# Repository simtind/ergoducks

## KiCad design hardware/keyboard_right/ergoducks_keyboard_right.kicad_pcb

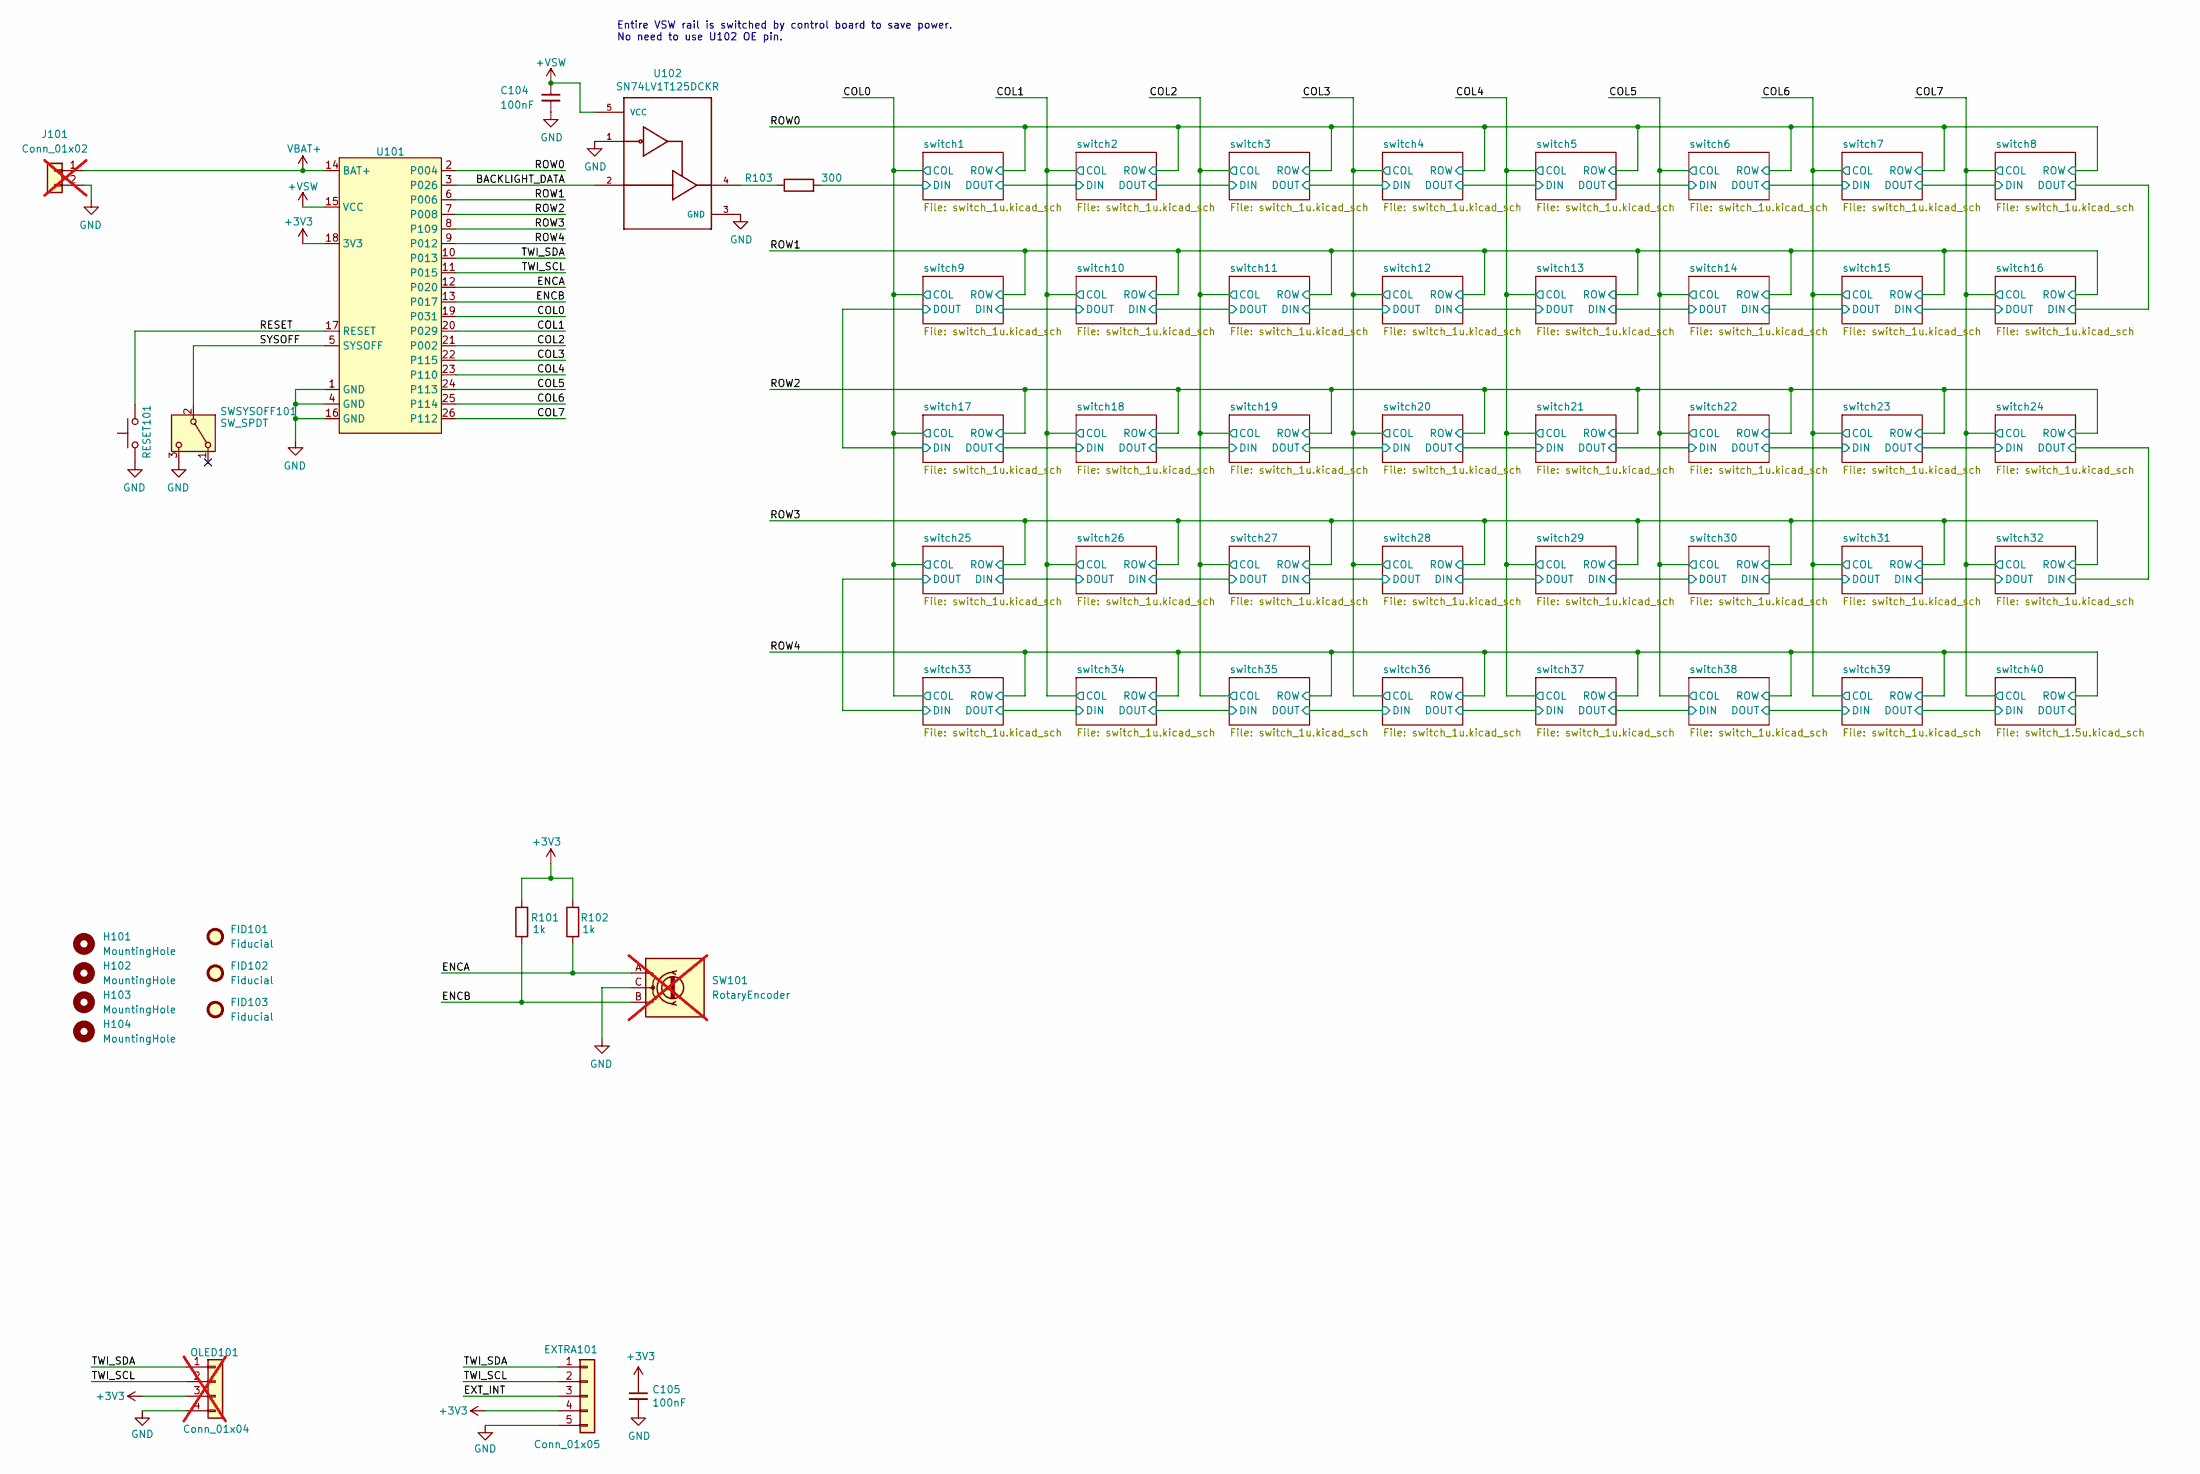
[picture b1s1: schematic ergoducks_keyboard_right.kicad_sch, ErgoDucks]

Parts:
C104, C105: 100nF; C_0402_1005Metric; Mouser partno 187-CL10B104JB8NNNC
EXTRA101: Conn_01x05; PinHeader_1x05_P2.54mm_Vertical
FID101, FID102, FID103: Fiducial; Fiducial_0.5mm_Mask1mm
H101, H102, H103, H104: MountingHole; MountingHole_2.2mm_M2
J101: Conn_01x02; JST_PH_S2B-PH-K_1x02_P2.00mm_Horizontal; not fitted
OLED101: Conn_01x04; PinHeader_1x04_P2.54mm_Vertical; not fitted
R101, R102: 1k; R_0603_1608Metric_Pad0.98x0.95mm_HandSolder; Mouser partno 667-ERJ-H3ED3000V
R103: 300; R_0603_1608Metric_Pad0.98x0.95mm_HandSolder; Mouser partno 667-ERJ-H3ED3000V
RESET101: SW_Push; SW_SPST_B3U-1000P-B; LCSC C561515
SW101: RotaryEncoder; RotaryEncoder_Alps_EC11E-Switch_Vertical_H20mm_MountingHoles; not fitted
SWSYSOFF101: SW_SPDT; SW_SPDT_CK_JS102011SAQN; LCSC C221660
U101: graviton-keycon
U102: SN74LV1T125DCKR; SOT-23-5; Mouser partno 595-SN74LV1T125DCKR

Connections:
+3V3: C105.1, EXTRA101.4, OLED101.3, R101.2, R102.2, U101.18 (3V3)
+VSW: C104.1, U101.15 (VCC), U102.5 (VCC); also elsewhere on the board
/BACKLIGHT_DATA: U101.3 (P026), U102.2
/COL0: U101.19 (P031); also elsewhere on the board
/COL1: U101.20 (P029); also elsewhere on the board
/COL2: U101.21 (P002); also elsewhere on the board
/COL3: U101.22 (P115); also elsewhere on the board
/COL4: U101.23 (P110); also elsewhere on the board
/COL5: U101.24 (P113); also elsewhere on the board
/COL6: U101.25 (P114); also elsewhere on the board
/COL7: U101.26 (P112); also elsewhere on the board
/ENCA: R102.1, SW101.A, U101.12 (P020)
/ENCB: R101.1, SW101.B, U101.13 (P017)
/EXT_INT: EXTRA101.3
/RESET: RESET101.1, U101.17 (RESET)
/ROW0: U101.2 (P004); also elsewhere on the board
/ROW1: U101.6; also elsewhere on the board
/ROW2: U101.7 (P008); also elsewhere on the board
/ROW3: U101.8 (P109); also elsewhere on the board
/ROW4: U101.9 (P012); also elsewhere on the board
/SYSOFF: SWSYSOFF101.2 (B), U101.5 (SYSOFF)
/TWI_SCL: EXTRA101.2, OLED101.2, U101.11 (P015)
/TWI_SDA: EXTRA101.1, OLED101.1, U101.10 (P013)
/switch1/DIN: R103.2; also elsewhere on the board
GND: C104.2, C105.2, EXTRA101.5, J101.2, OLED101.4, RESET101.2, SW101.C, SWSYSOFF101.3 (C), U101.1 (GND), U101.4 (GND), U101.16 (GND), U102.1, U102.3 (GND); also elsewhere on the board
unnamed: R103.1, U102.4
VBAT+: J101.1, U101.14 (BAT+)

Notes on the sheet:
Entire VSW rail is switched by control board to save power. No need to use U102 OE pin.

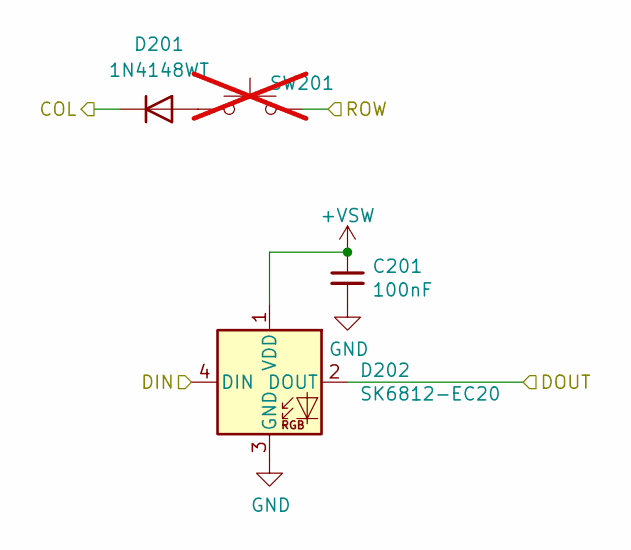
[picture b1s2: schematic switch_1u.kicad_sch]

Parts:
C201: 100nF; C_0402_1005Metric; Mouser partno 187-CL10B104JB8NNNC
D201: 1N4148WT; D_SOD-523; LCSC C27748
D202: SK6812-EC20; sk6812-ec20; Digikey partno 1528-4960-ND
SW201: SW_Hotswap_Kailh_Choc_V1V2_1.00u; Mouser partno 540-MX1A-G1NA; not fitted

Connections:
+VSW: C201.1, D202.1 (VDD); also elsewhere on the board
/COL0: D201.1 (K); also elsewhere on the board
/ROW0: SW201.2; also elsewhere on the board
/switch1/DIN: D202.4 (DIN); also elsewhere on the board
/switch1/DOUT: D202.2 (DOUT); also elsewhere on the board
GND: C201.2, D202.3 (GND); also elsewhere on the board
unnamed: D201.2 (A), SW201.1

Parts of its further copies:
C301, C401, C501, C601, C701, C801, C901, C1001, C1101, C1201, C1301, C1401, C1501, C1601, C1701, C1801, C1901, C2001, C2101, C2201, C2301, C2401, C2501, C2601, C2701, C2801, C2901, C3001, C3101, C3201, C3301, C3401, C3501, C3601, C3701, C3801, C3901, C4001: 100nF; C_0402_1005Metric; Mouser partno 187-CL10B104JB8NNNC
D301, D401, D501, D601, D701, D801, D901, D1001, D1101, D1201, D1301, D1401, D1501, D1601, D1701, D1801, D1901, D2001, D2101, D2201, D2301, D2401, D2501, D2601, D2701, D2801, D2901, D3001, D3101, D3201, D3301, D3401, D3501, D3601, D3701, D3801, D3901, D4001: 1N4148WT; D_SOD-523; LCSC C27748
D302, D402, D502, D602, D702, D802, D902, D1002, D1102, D1202, D1302, D1402, D1502, D1602, D1702, D1802, D1902, D2002, D2102, D2202, D2302, D2402, D2502, D2602, D2702, D2802, D2902, D3002, D3102, D3202, D3302, D3402, D3502, D3602, D3702, D3802, D3902, D4002: SK6812-EC20; sk6812-ec20; Digikey partno 1528-4960-ND
SW301, SW401, SW501, SW601, SW701, SW801, SW901, SW1001, SW1101, SW1201, SW1301, SW1401, SW1501, SW1601, SW1701, SW1801, SW1901, SW2001, SW2101, SW2201, SW2301, SW2401, SW2501, SW2601, SW2701, SW2801, SW2901, SW3001, SW3101, SW3201, SW3301, SW3401, SW3501, SW3601, SW3701, SW3801, SW3901, SW4001: SW_Hotswap_Kailh_Choc_V1V2_1.00u; Mouser partno 540-MX1A-G1NA; not fitted

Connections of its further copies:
+VSW: C301.1, C401.1, C501.1, C601.1, C701.1, C801.1, C901.1, C1001.1, C1101.1, C1201.1, C1301.1, C1401.1, C1501.1, C1601.1, C1701.1, C1801.1, C1901.1, C2001.1, C2101.1, C2201.1, C2301.1, C2401.1, C2501.1, C2601.1, C2701.1, C2801.1, C2901.1, C3001.1, C3101.1, C3201.1, C3301.1, C3401.1, C3501.1, C3601.1, C3701.1, C3801.1, C3901.1, C4001.1, D302.1 (VDD), D402.1 (VDD), D502.1 (VDD), D602.1 (VDD), D702.1 (VDD), D802.1 (VDD), D902.1 (VDD), D1002.1 (VDD), D1102.1 (VDD), D1202.1 (VDD), D1302.1 (VDD), D1402.1 (VDD), D1502.1 (VDD), D1602.1 (VDD), D1702.1 (VDD), D1802.1 (VDD), D1902.1 (VDD), D2002.1 (VDD), D2102.1 (VDD), D2202.1 (VDD), D2302.1 (VDD), D2402.1 (VDD), D2502.1 (VDD), D2602.1 (VDD), D2702.1 (VDD), D2802.1 (VDD), D2902.1 (VDD), D3002.1 (VDD), D3102.1 (VDD), D3202.1 (VDD), D3302.1 (VDD), D3402.1 (VDD), D3502.1 (VDD), D3602.1 (VDD), D3702.1 (VDD), D3802.1 (VDD), D3902.1 (VDD), D4002.1 (VDD); also elsewhere on the board
/COL0: D1001.1 (K), D1801.1 (K), D2601.1 (K), D3401.1 (K); also elsewhere on the board
/COL1: D301.1 (K), D1101.1 (K), D1901.1 (K), D2701.1 (K), D3501.1 (K); also elsewhere on the board
/COL2: D401.1 (K), D1201.1 (K), D2001.1 (K), D2801.1 (K), D3601.1 (K); also elsewhere on the board
/COL3: D501.1 (K), D1301.1 (K), D2101.1 (K), D2901.1 (K), D3701.1 (K); also elsewhere on the board
/COL4: D601.1 (K), D1401.1 (K), D2201.1 (K), D3001.1 (K), D3801.1 (K); also elsewhere on the board
/COL5: D701.1 (K), D1501.1 (K), D2301.1 (K), D3101.1 (K), D3901.1 (K); also elsewhere on the board
/COL6: D801.1 (K), D1601.1 (K), D2401.1 (K), D3201.1 (K), D4001.1 (K); also elsewhere on the board
/COL7: D901.1 (K), D1701.1 (K), D2501.1 (K), D3301.1 (K); also elsewhere on the board
/ROW0: SW301.2, SW401.2, SW501.2, SW601.2, SW701.2, SW801.2, SW901.2; also elsewhere on the board
/ROW1: SW1001.2, SW1101.2, SW1201.2, SW1301.2, SW1401.2, SW1501.2, SW1601.2, SW1701.2; also elsewhere on the board
/ROW2: SW1801.2, SW1901.2, SW2001.2, SW2101.2, SW2201.2, SW2301.2, SW2401.2, SW2501.2; also elsewhere on the board
/ROW3: SW2601.2, SW2701.2, SW2801.2, SW2901.2, SW3001.2, SW3101.2, SW3201.2, SW3301.2; also elsewhere on the board
/ROW4: SW3401.2, SW3501.2, SW3601.2, SW3701.2, SW3801.2, SW3901.2, SW4001.2; also elsewhere on the board
/switch1/DOUT: D302.4 (DIN); also elsewhere on the board
/switch2/DOUT: D302.2 (DOUT), D402.4 (DIN)
/switch3/DOUT: D402.2 (DOUT), D502.4 (DIN)
/switch4/DOUT: D502.2 (DOUT), D602.4 (DIN)
/switch5/DOUT: D602.2 (DOUT), D702.4 (DIN)
/switch6/DOUT: D702.2 (DOUT), D802.4 (DIN)
/switch7/DOUT: D802.2 (DOUT), D902.4 (DIN)
/switch10/DIN: D1102.4 (DIN), D1202.2 (DOUT)
/switch10/DOUT: D1002.4 (DIN), D1102.2 (DOUT)
/switch11/DIN: D1202.4 (DIN), D1302.2 (DOUT)
/switch12/DIN: D1302.4 (DIN), D1402.2 (DOUT)
/switch13/DIN: D1402.4 (DIN), D1502.2 (DOUT)
/switch14/DIN: D1502.4 (DIN), D1602.2 (DOUT)
/switch15/DIN: D1602.4 (DIN), D1702.2 (DOUT)
/switch16/DIN: D902.2 (DOUT), D1702.4 (DIN)
/switch17/DIN: D1002.2 (DOUT), D1802.4 (DIN)
/switch17/DOUT: D1802.2 (DOUT), D1902.4 (DIN)
/switch18/DOUT: D1902.2 (DOUT), D2002.4 (DIN)
/switch19/DOUT: D2002.2 (DOUT), D2102.4 (DIN)
/switch20/DOUT: D2102.2 (DOUT), D2202.4 (DIN)
/switch21/DOUT: D2202.2 (DOUT), D2302.4 (DIN)
/switch22/DOUT: D2302.2 (DOUT), D2402.4 (DIN)
/switch23/DOUT: D2402.2 (DOUT), D2502.4 (DIN)
/switch24/DOUT: D2502.2 (DOUT), D3302.4 (DIN)
/switch25/DIN: D2602.4 (DIN), D2702.2 (DOUT)
/switch25/DOUT: D2602.2 (DOUT), D3402.4 (DIN)
/switch26/DIN: D2702.4 (DIN), D2802.2 (DOUT)
/switch27/DIN: D2802.4 (DIN), D2902.2 (DOUT)
/switch28/DIN: D2902.4 (DIN), D3002.2 (DOUT)
/switch29/DIN: D3002.4 (DIN), D3102.2 (DOUT)
/switch30/DIN: D3102.4 (DIN), D3202.2 (DOUT)
/switch31/DIN: D3202.4 (DIN), D3302.2 (DOUT)
/switch33/DOUT: D3402.2 (DOUT), D3502.4 (DIN)
/switch34/DOUT: D3502.2 (DOUT), D3602.4 (DIN)
/switch35/DOUT: D3602.2 (DOUT), D3702.4 (DIN)
/switch36/DOUT: D3702.2 (DOUT), D3802.4 (DIN)
/switch37/DOUT: D3802.2 (DOUT), D3902.4 (DIN)
/switch38/DOUT: D3902.2 (DOUT), D4002.4 (DIN)
/switch39/DOUT: D4002.2 (DOUT); also elsewhere on the board
GND: C301.2, C401.2, C501.2, C601.2, C701.2, C801.2, C901.2, C1001.2, C1101.2, C1201.2, C1301.2, C1401.2, C1501.2, C1601.2, C1701.2, C1801.2, C1901.2, C2001.2, C2101.2, C2201.2, C2301.2, C2401.2, C2501.2, C2601.2, C2701.2, C2801.2, C2901.2, C3001.2, C3101.2, C3201.2, C3301.2, C3401.2, C3501.2, C3601.2, C3701.2, C3801.2, C3901.2, C4001.2, D302.3 (GND), D402.3 (GND), D502.3 (GND), D602.3 (GND), D702.3 (GND), D802.3 (GND), D902.3 (GND), D1002.3 (GND), D1102.3 (GND), D1202.3 (GND), D1302.3 (GND), D1402.3 (GND), D1502.3 (GND), D1602.3 (GND), D1702.3 (GND), D1802.3 (GND), D1902.3 (GND), D2002.3 (GND), D2102.3 (GND), D2202.3 (GND), D2302.3 (GND), D2402.3 (GND), D2502.3 (GND), D2602.3 (GND), D2702.3 (GND), D2802.3 (GND), D2902.3 (GND), D3002.3 (GND), D3102.3 (GND), D3202.3 (GND), D3302.3 (GND), D3402.3 (GND), D3502.3 (GND), D3602.3 (GND), D3702.3 (GND), D3802.3 (GND), D3902.3 (GND), D4002.3 (GND); also elsewhere on the board
unnamed: D301.2 (A), SW301.1
unnamed: D401.2 (A), SW401.1
unnamed: D501.2 (A), SW501.1
unnamed: D601.2 (A), SW601.1
unnamed: D701.2 (A), SW701.1
unnamed: D801.2 (A), SW801.1
unnamed: D901.2 (A), SW901.1
unnamed: D1001.2 (A), SW1001.1
unnamed: D1101.2 (A), SW1101.1
unnamed: D1201.2 (A), SW1201.1
unnamed: D1301.2 (A), SW1301.1
unnamed: D1401.2 (A), SW1401.1
unnamed: D1501.2 (A), SW1501.1
unnamed: D1601.2 (A), SW1601.1
unnamed: D1701.2 (A), SW1701.1
unnamed: D1801.2 (A), SW1801.1
unnamed: D1901.2 (A), SW1901.1
unnamed: D2001.2 (A), SW2001.1
unnamed: D2101.2 (A), SW2101.1
unnamed: D2201.2 (A), SW2201.1
unnamed: D2301.2 (A), SW2301.1
unnamed: D2401.2 (A), SW2401.1
unnamed: D2501.2 (A), SW2501.1
unnamed: D2601.2 (A), SW2601.1
unnamed: D2701.2 (A), SW2701.1
unnamed: D2801.2 (A), SW2801.1
unnamed: D2901.2 (A), SW2901.1
unnamed: D3001.2 (A), SW3001.1
unnamed: D3101.2 (A), SW3101.1
unnamed: D3201.2 (A), SW3201.1
unnamed: D3301.2 (A), SW3301.1
unnamed: D3401.2 (A), SW3401.1
unnamed: D3501.2 (A), SW3501.1
unnamed: D3601.2 (A), SW3601.1
unnamed: D3701.2 (A), SW3701.1
unnamed: D3801.2 (A), SW3801.1
unnamed: D3901.2 (A), SW3901.1
unnamed: D4001.2 (A), SW4001.1

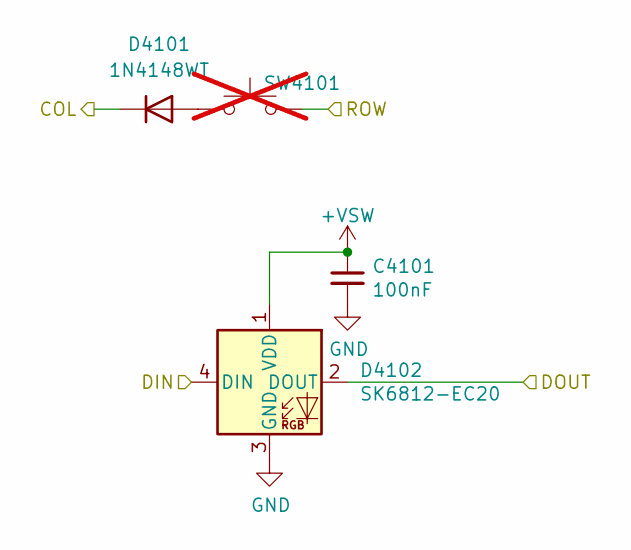
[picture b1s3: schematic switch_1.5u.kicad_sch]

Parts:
C4101: 100nF; C_0402_1005Metric; Mouser partno 187-CL10B104JB8NNNC
D4101: 1N4148WT; D_SOD-523; LCSC C27748
D4102: SK6812-EC20; sk6812-ec20; Digikey partno 1528-4960-ND
SW4101: SW_Hotswap_Kailh_Choc_V1V2_1.50u; Mouser partno 540-MX1A-G1NA; not fitted

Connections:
+VSW: C4101.1, D4102.1 (VDD); also elsewhere on the board
/COL7: D4101.1 (K); also elsewhere on the board
/ROW4: SW4101.2; also elsewhere on the board
/switch39/DOUT: D4102.4 (DIN); also elsewhere on the board
/switch40/DOUT: D4102.2 (DOUT)
GND: C4101.2, D4102.3 (GND); also elsewhere on the board
unnamed: D4101.2 (A), SW4101.1

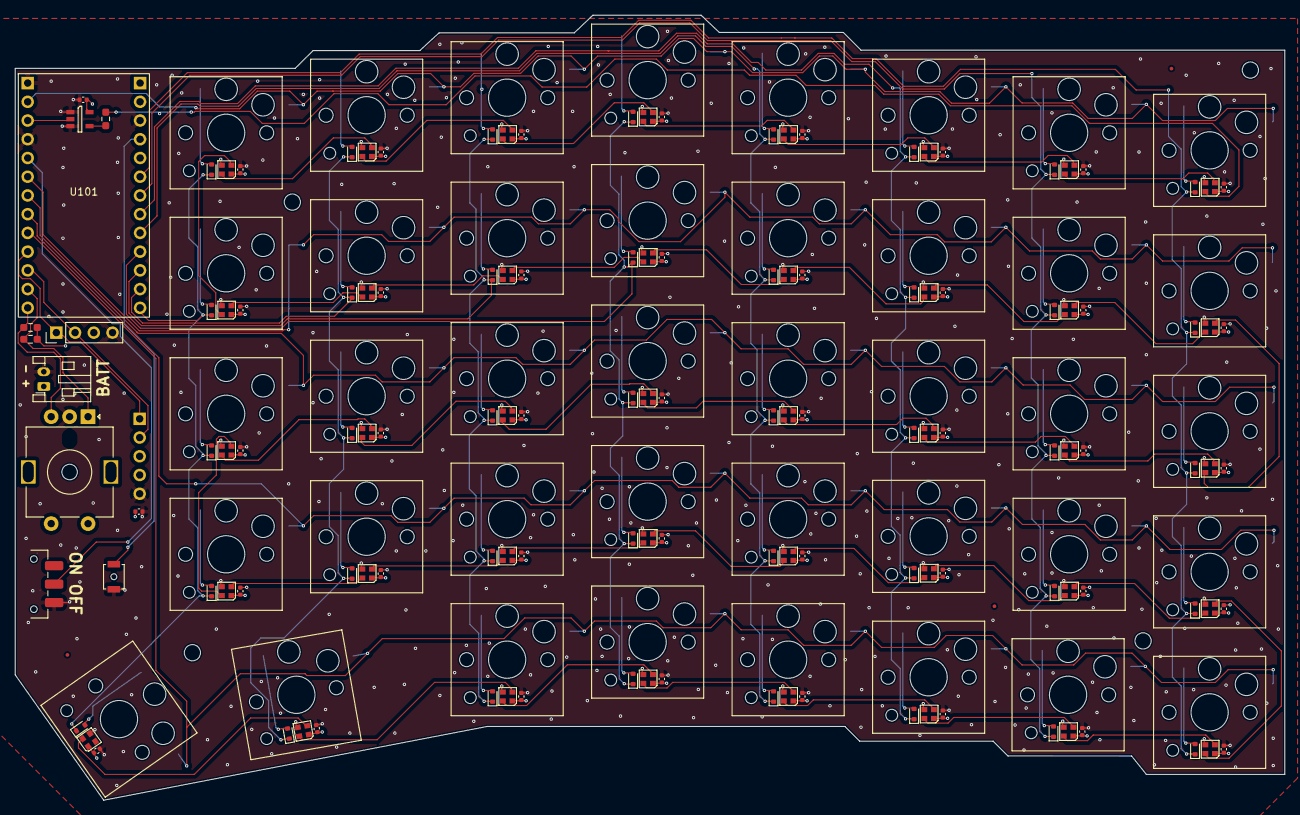
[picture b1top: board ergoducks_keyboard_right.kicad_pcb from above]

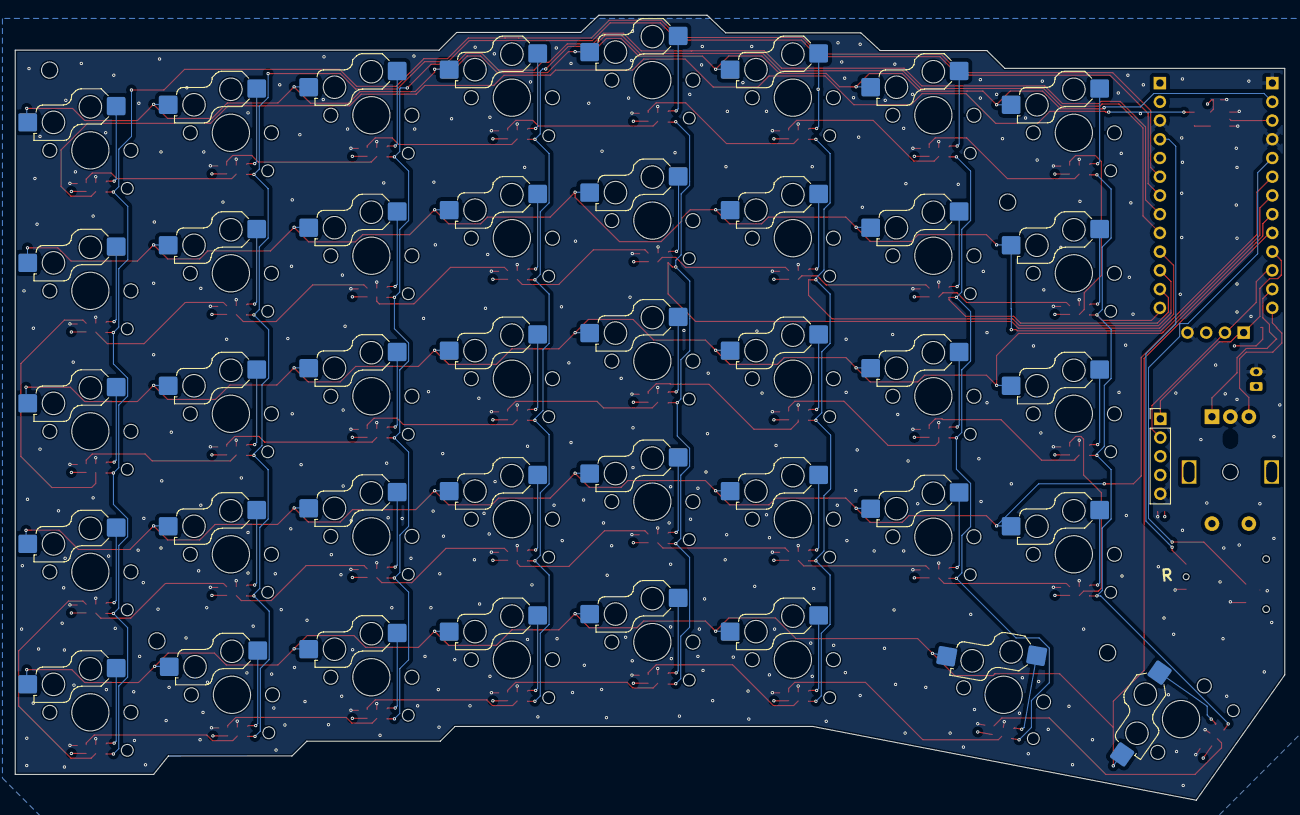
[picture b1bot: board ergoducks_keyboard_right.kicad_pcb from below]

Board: 4 copper layers, 172.1 x 106.4 mm, 180 parts (2 on the bottom side), 105 nets.

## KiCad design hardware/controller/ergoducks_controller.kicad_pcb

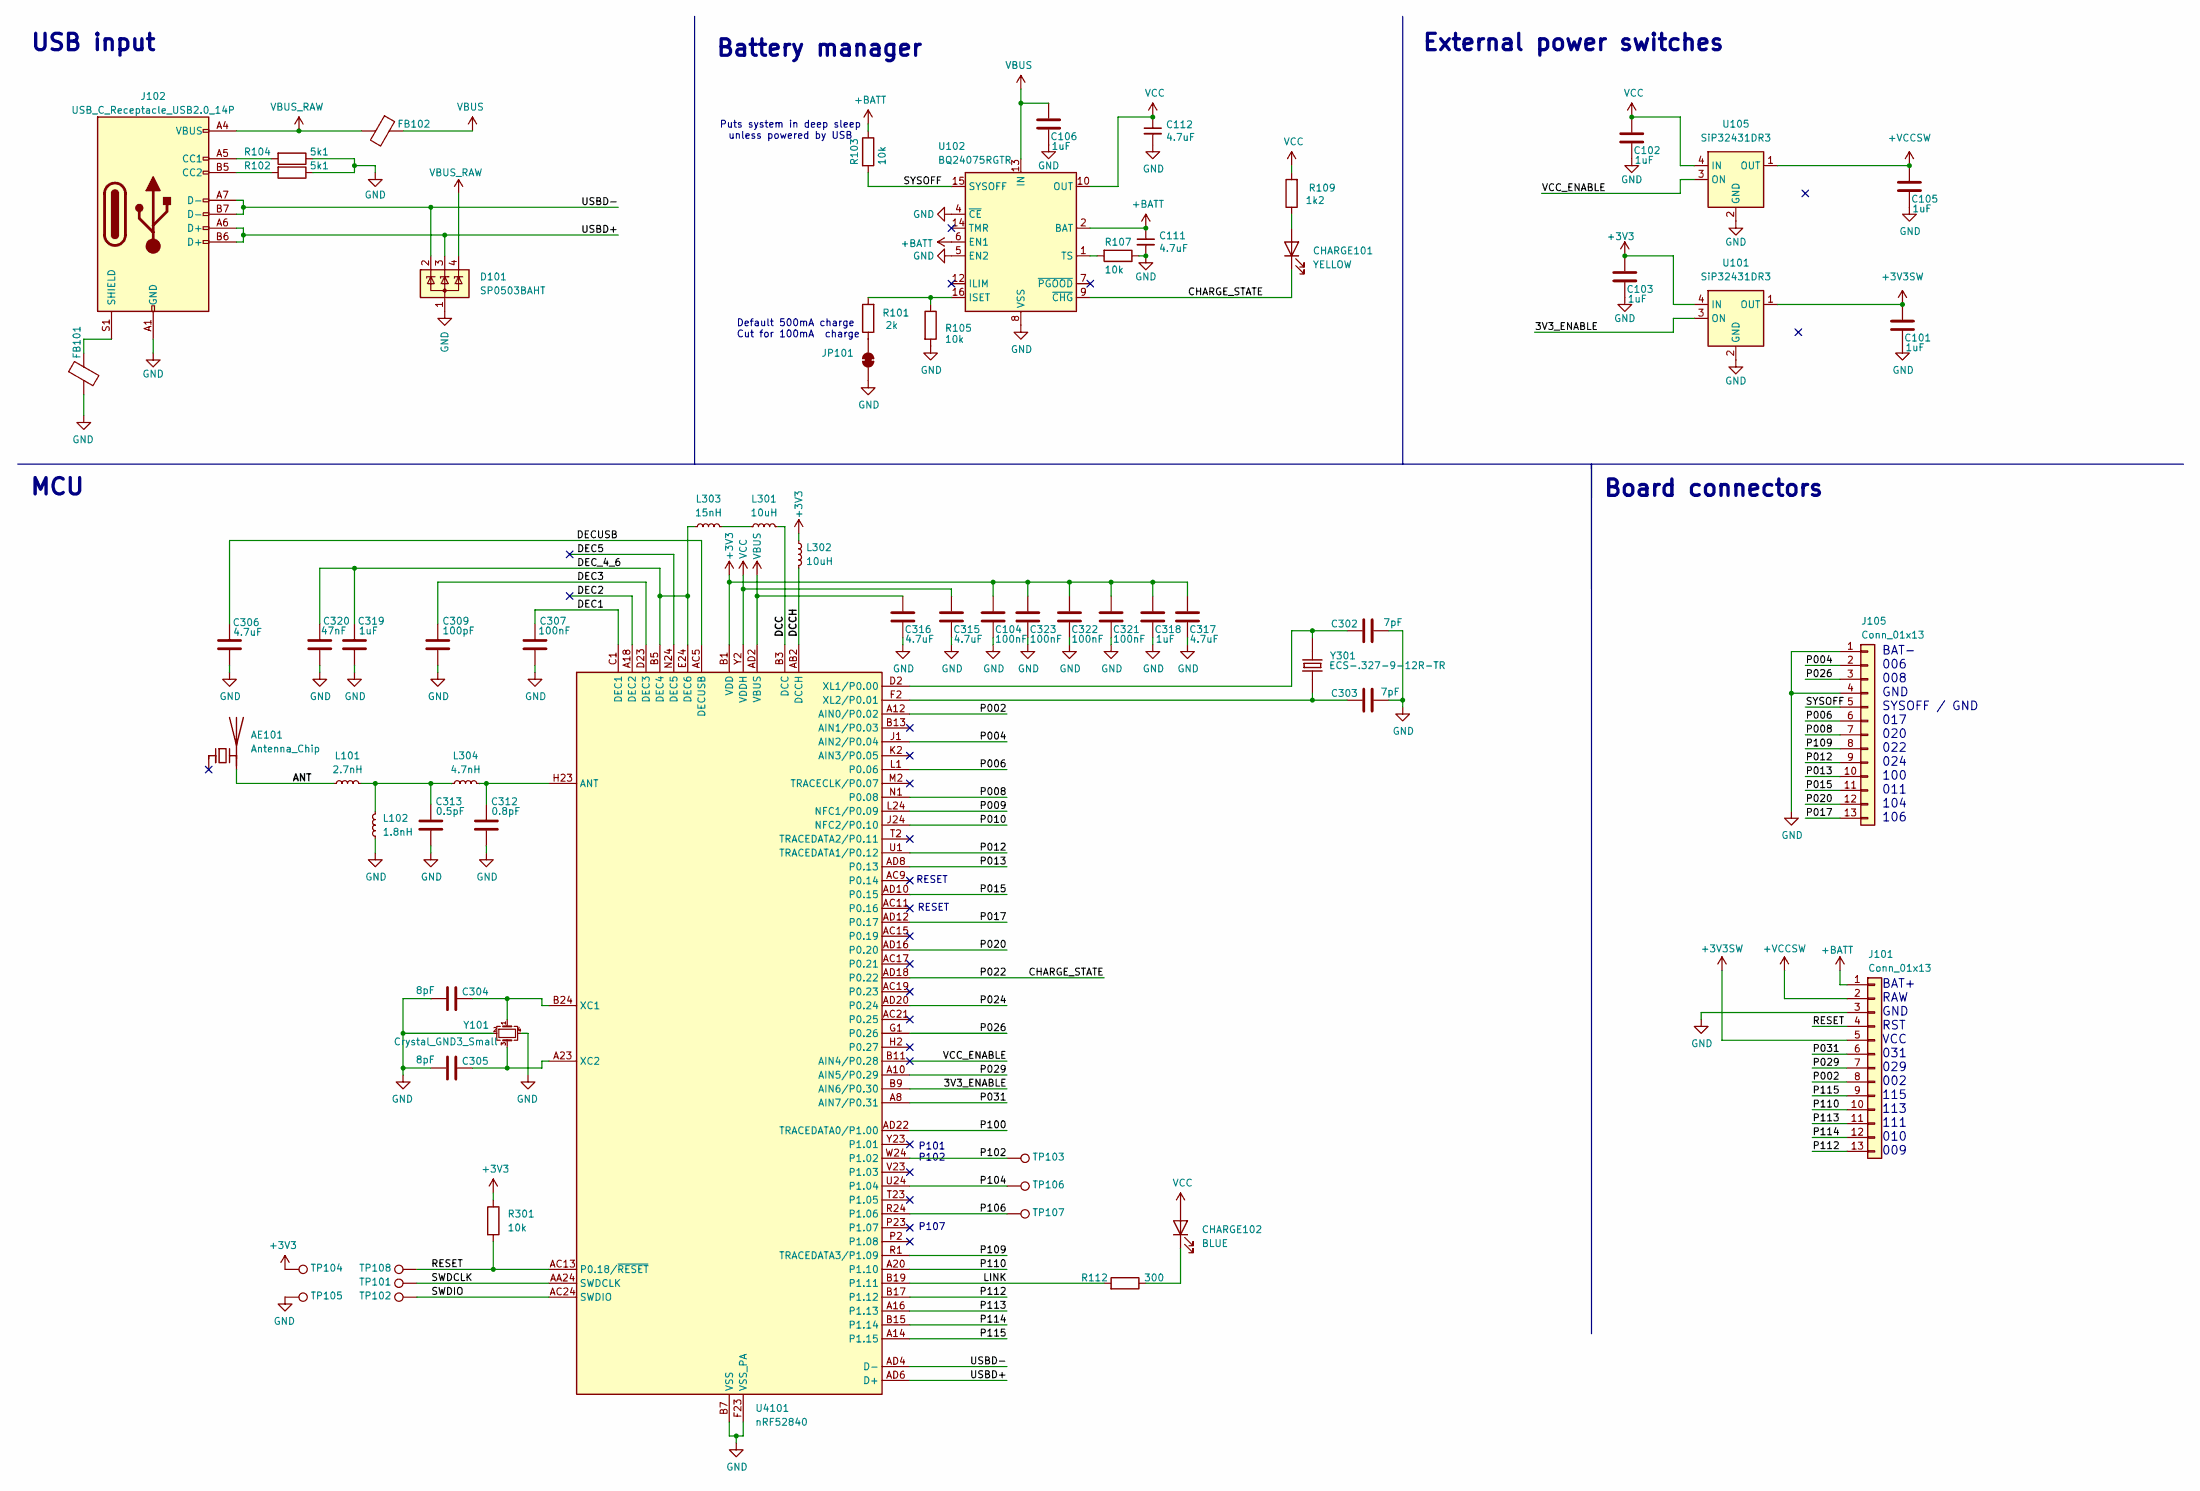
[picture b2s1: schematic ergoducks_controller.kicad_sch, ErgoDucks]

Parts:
AE101: Antenna_Chip; Johanson_2450AT43F0100_wwithpads_cortyard; Part Number 2450AT43B100E; LCSC C2917721
C101, C102, C103, C105, C106, C318, C319: 1uF; C_0201_0603Metric; Part Number GRM033R61A105ME44D; LCSC C76935
C104, C307, C321, C322, C323: 100nF; C_0201_0603Metric; Part Number GRM033Z71C104KE14D; LCSC C668346
C111, C112: 4.7uF; C_0402_1005Metric; Mouser partno 187-CL10A475KQ8NNNC
C302, C303: 7pF; C_0201_0603Metric; Part Number GRM0335C1H7R0BA01D; LCSC C161436
C304, C305: 8pF; C_0201_0603Metric; Part Number GRM0335C1H8R0BA01D; LCSC C237417
C306, C315, C316, C317: 4.7uF; C_0402_1005Metric; Part Number GRM155R61E475ME15DGRM155R61E475ME15D; LCSC C2858031
C309: 100pF; C_0201_0603Metric; Part Number GRM0335C1H101JA01D; LCSC C76922
C312: 0.8pF; C_0201_0603Metric; Part Number GRM0335C1HR80WA01D; LCSC C385012
C313: 0.5pF; C_0201_0603Metric; Part Number GRM0335C1HR50BA01D; LCSC C85920
C320: 47nF; C_0201_0603Metric; Part Number GRM033C80J473KE19D; LCSC C782148
CHARGE101: YELLOW; D_0402_1005Metric; Part Number XL-1005UYC; LCSC C25503856
CHARGE102: BLUE; D_0402_1005Metric; Part Number SZYY0402B; LCSC C434447
D101: SP0503BAHT; SOT-143; Part Number SP0503BAHTG; LCSC C7074
FB101, FB102: 120R/0.55A; R_0201_0603Metric; Mouser partno 673-PE-0603PFB121ST
J101, J105: Conn_01x13; PinHeader_1x13_P2.54mm_Vertical
J102: USB_C_Receptacle_USB2.0_14P; JAE_DX07B024JJ2R1500; Part Number DX07B024JJ1R1500; LCSC C2977280
JP101: Cut for 100mA charge; SolderJumper-2_P1mm_Bridged_RoundedPad0.8x1mm
L101: 2.7nH; L_0201_0603Metric; Part Number LQP03TN2N7B02D; LCSC C98043
L102: 1.8nH; L_0201_0603Metric; Part Number LQP03TN1N8B02D; LCSC C98040
L301, L302: 10uH; L_0603_1608Metric; Part Number LQM18FN100M00D; LCSC C86083
L303: 15nH; L_0402_1005Metric; Part Number LQG15HS15NJ02D; LCSC C86059
L304: 4.7nH; L_0201_0603Metric; Part Number LQP03HQ4N7H02D; LCSC C237443
R101: 2k; R_0201_0603Metric; Mouser partno 667-ERJ-H3ED3000V
R102, R104: 5k1; R_0201_0603Metric; Mouser partno 603-RC0603JR-075K1L
R103, R105, R107: 10k; R_0201_0603Metric; Mouser partno 667-ERJ-H3ED1002V
R109: 1k2; R_0201_0603Metric; Mouser partno 667-ERJ-H3ED3000V
R112: 300; R_0201_0603Metric; Mouser partno 667-ERJ-H3ED3000V
R301: 10k; R_0201_0603Metric; Part Number RC0201FR-0710KL; LCSC C106225
TP101, TP108: SWDCLK; TestPoint_Pad_D1.0mm
TP102: SWDIO; TestPoint_Pad_D1.0mm
TP103, TP104, TP106, TP107: 3V3; TestPoint_Pad_D1.0mm
TP105: GND; TestPoint_Pad_D1.0mm
U101, U105: SiP32431DR3; SOT-363_SC-70-6; Part Number SIP32431DR3-T1GE3; LCSC C141606
U102: BQ24075RGTR; VQFN-16-1EP_3x3mm_P0.5mm_EP1.6x1.6mm; Mouser partno 595-BQ24079TRGTR; Digikey partno 296-BQ24079QWRGTRQ1CT-ND
U4101: nRF52840; Nordic_AQFN-73-1EP_7x7mm_P0.5mm; Part Number NRF52840-QIAA-R; LCSC C190794
Y101: Crystal_GND3_Small; Crystal_SMD_SeikoEpson_FA128-4Pin_2.0x1.6mm; Part Number Q22FA12800025; LCSC C187794
Y301: ECS-.327-9-12R-TR; Crystal_SMD_2012-2Pin_2.0x1.2mm_HandSoldering; Mouser partno 520-.327-9-12R-T

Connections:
+3V3: C103.2, C104.2, C317.2, C318.2, C321.2, C322.2, C323.2, L302.1, R301.1, TP104.1, U101.4 (IN), U4101.A22 (VDD), U4101.AD14 (VDD), U4101.AD23 (VDD), U4101.B1 (VDD), U4101.W1 (VDD)
+3V3SW: C101.2, J101.5, U101.1 (OUT)
+BATT: C111.1, J101.1, R103.1, U102.2 (BAT), U102.3 (BAT), U102.6 (EN1)
+VCCSW: C105.2, J101.2, U105.1 (OUT)
/3V3_ENABLE: U101.3 (ON), U4101.B9 (AIN6/P0.30)
/ANT: AE101.2 (PCB_Trace), L101.1
/CHARGE_STATE: CHARGE101.1 (K), U102.9 (~CHG), U4101.AD18 (P0.22)
/DCC: L301.2, U4101.B3 (DCC)
/DCCH: L302.2, U4101.AB2 (DCCH)
/DEC1: C307.2, U4101.C1 (DEC1)
/DEC2: U4101.A18 (DEC2)
/DEC3: C309.2, U4101.D23 (DEC3)
/DEC5: U4101.N24 (DEC5)
/DECUSB: C306.2, U4101.AC5 (DECUSB)
/DEC_4_6: C319.2, C320.2, L303.1, U4101.B5 (DEC4), U4101.E24 (DEC6)
/LINK: R112.2, U4101.B19 (P1.11)
/P002: J101.8, U4101.A12 (AIN0/P0.02)
/P004: J105.2, U4101.J1 (AIN2/P0.04)
/P006: J105.6, U4101.L1 (P0.06)
/P008: J105.7, U4101.N1 (P0.08)
/P009: U4101.L24 (NFC1/P0.09)
/P010: U4101.J24 (NFC2/P0.10)
/P012: J105.9, U4101.U1 (TRACEDATA1/P0.12)
/P013: J105.10, U4101.AD8 (P0.13)
/P015: J105.11, U4101.AD10 (P0.15)
/P017: J105.13, U4101.AD12 (P0.17)
/P020: J105.12, U4101.AD16 (P0.20)
/P024: U4101.AD20 (P0.24)
/P026: J105.3, U4101.G1 (P0.26)
/P029: J101.7, U4101.A10 (AIN5/P0.29)
/P031: J101.6, U4101.A8 (AIN7/P0.31)
/P100: U4101.AD22 (TRACEDATA0/P1.00)
/P102: TP103.1, U4101.W24 (P1.02)
/P104: TP106.1, U4101.U24 (P1.04)
/P106: TP107.1, U4101.R24 (P1.06)
/P109: J105.8, U4101.R1 (TRACEDATA3/P1.09)
/P110: J101.10, U4101.A20 (P1.10)
/P112: J101.13, U4101.B17 (P1.12)
/P113: J101.11, U4101.A16 (P1.13)
/P114: J101.12, U4101.B15 (P1.14)
/P115: J101.9, U4101.A14 (P1.15)
/RESET: J101.4, R301.2, TP108.1, U4101.AC13 (P0.18/~RESET)
/SWDCLK: TP101.1, U4101.AA24 (SWDCLK)
/SWDIO: TP102.1, U4101.AC24 (SWDIO)
/SYSOFF: J105.5, R103.2, U102.15 (SYSOFF)
/USBD+: D101.3 (K), J102.A6 (D+), J102.B6 (D+), U4101.AD6 (D+)
/USBD-: D101.2 (K), J102.A7 (D-), J102.B7 (D-), U4101.AD4 (D-)
/VCC_ENABLE: U105.3 (ON), U4101.B11 (AIN4/P0.28)
GND: C101.1, C102.1, C103.1, C104.1, C105.1, C106.1, C111.2, C112.2, C302.2, C303.2, C304.2, C305.2, C306.1, C307.1, C309.1, C312.1, C313.1, C315.1, C316.1, C317.1, C318.1, C319.1, C320.1, C321.1, C322.1, C323.1, D101.1 (A), FB101.2, J101.3, J102.A1 (GND), J102.A12 (GND), J102.B1 (GND), J102.B12 (GND), J105.1, J105.4, JP101.1 (A), L102.1, R102.1, R104.1, R105.2, R107.1, TP105.1, U101.2 (GND), U101.5 (GND), U102.4 (~CE), U102.5 (EN2), U102.8 (VSS), U102.17 (VSS), U105.2 (GND), U105.5 (GND), U4101.B7 (VSS), U4101.EP (VSS), U4101.F23 (VSS_PA), Y101.2, Y101.4
unnamed: C313.2, L101.2, L102.2, L304.1
unnamed: CHARGE101.2 (A), R109.1
unnamed: CHARGE102.1 (K), R112.1
unnamed: J102.A5 (CC1), R104.2
unnamed: J102.B5 (CC2), R102.2
unnamed: FB101.1, J102.S1 (SHIELD)
unnamed: JP101.2 (B), R101.1
unnamed: L301.1, L303.2
unnamed: R101.2, R105.1, U102.16 (ISET)
unnamed: R107.2, U102.1 (TS)
unnamed: C312.2, L304.2, U4101.H23 (ANT)
unnamed: C304.1, U4101.B24 (XC1), Y101.1
unnamed: C305.1, U4101.A23 (XC2), Y101.3
unnamed: C302.1, U4101.D2 (XL1/P0.00), Y301.1
unnamed: C303.1, U4101.F2 (XL2/P0.01), Y301.2
VBUS: C106.2, C316.2, FB102.1, U102.13 (IN), U4101.AD2 (VBUS)
VBUS_RAW: D101.4 (K), FB102.2, J102.A4 (VBUS), J102.A9 (VBUS), J102.B4 (VBUS), J102.B9 (VBUS)
VCC: C102.2, C112.1, C315.2, CHARGE102.2 (A), R109.2, U102.10 (OUT), U102.11 (OUT), U105.4 (IN), U4101.Y2 (VDDH)

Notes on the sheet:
USB input
BAT+ RAW GND RST VCC 031 029 002 115 113 111 010 009
Default 500mA charge Cut for 100mA charge
External power switches
P101 P102
MCU
P107
RESET
Battery manager
BAT- 006 008 GND SYSOFF / GND 017 020 022 024 100 011 104 106
Puts system in deep sleep unless powered by USB
Board connectors

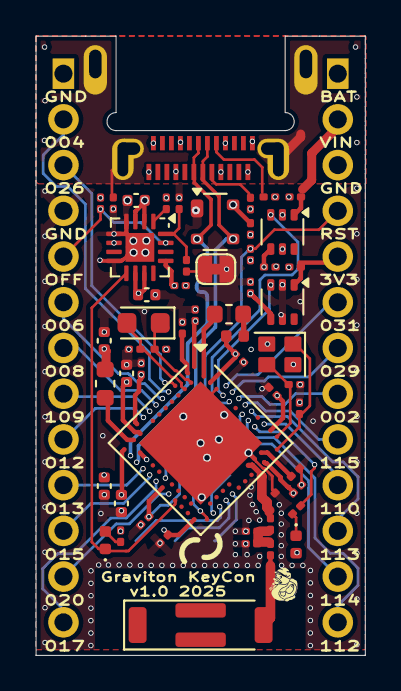
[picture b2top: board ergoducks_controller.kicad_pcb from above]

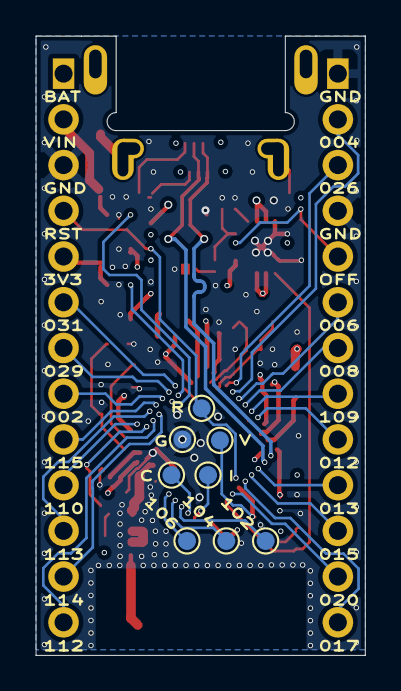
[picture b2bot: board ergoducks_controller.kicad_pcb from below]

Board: 6 copper layers, 18.3 x 34.4 mm, 65 parts (10 on the bottom side), 61 nets.

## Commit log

2025-08-08 Check in project
2025-08-08 Add auto-saved version of pcb.
2025-09-15 Start rev 2
2025-09-15 Add keyboard layout
2025-09-15 Update keyboard layout
2025-12-31 Update after producion of rev 2
2025-12-31 Add firmware
2025-12-31 Set config and matrix file paths correctly
2025-12-31 Add default working directory
2025-12-31 Fix working dir setting
2025-12-31 Test
2025-12-31 Move source code so we're ZMK compatible
2025-12-31 Fix pinning
2025-12-31 Update with norwegian keymap
2025-12-31 Add sensor bindings
2025-12-31 Fix naming error
2025-12-31 fix cdc uart
2025-12-31 Fix missing include
2025-12-31 Add display support
2026-01-01 Support bootloader
2026-01-01 Syntax error
2026-01-01 Fix missing data
2026-01-01 Use main branch zmk
2026-01-01 tset
2026-01-01 Fix keymap syntrxxc error
2026-01-01 Fix dependency loop
2026-01-01 reorganize to fix issues with zephyr update
2026-01-01 select correct controller
2026-01-01 Fix keymap
2026-01-01 Build hexfile
2026-01-01 Fix keyboard pin mapping
2026-01-01 Even more keymap improvements
2026-01-01 Enable usb logging
2026-01-01 Even more keymaps
2026-01-01 Add backlight
2026-01-01 Use i2s for rgb backlight
2026-01-01 Select correct ws2812 driver
2026-01-01 Add missing include
2026-01-01 Fix ec11 trigger mode
2026-01-01 Define all pins for i2s
2026-01-01 rtt logging
2026-01-01 Fix keymap again
2026-01-02 Reduce max intensity for backlight.
2026-01-02 disable underglow
2026-01-02 Increase I2C log level
2026-01-02 update log level more
2026-01-02 Remove ext power handling
2026-01-02 Fixes
2026-01-02 Increase RTT buffer size
2026-01-02 Remove pro micro pin mappings
2026-01-02 Switch to usb logging
2026-01-02 Updated settings
2026-01-02 more settings
2026-01-02 Use zmk built-in logging
2026-01-02 Fix config markers
2026-01-02 Correct config name
2026-01-02 Wait a long time to initialize oled
2026-01-02 Remove display priority change
2026-01-02 Modify display inity priority
2026-01-02 Make lv and dispaly init sequentially
2026-01-02 Dump I2C messages
2026-01-02 Enable the deep logs
2026-01-02 REduce oled delay time?
2026-01-02 Keep sleep in same range as before?
2026-01-02 Cleanup config
2026-01-03 Make encoders scrollwheels
2026-01-03 Increase scroll response
2026-01-03 Even more beter encoder
2026-01-04 Update keymap
2026-05-24 Default-enable external power
2026-05-24 Use external regulators to control load switches instead of zmk
2026-05-24 Set correct pin polarity
2026-05-24 Try using leds?
2026-05-24 Device name
2026-05-24 Enable RGB leds
2026-05-24 Fix righth side pin mapping
2026-05-24 Reduce logging
2026-05-26 Add settings reset target
2026-05-26 Remove usb logging in right firmware
2026-05-26 Remove expolicit zmk usb logging enable.
2026-05-26 Switch central to right half
2026-05-26 Try to workaround broken oscillator
2026-05-26 Remove pro micro support
2026-05-26 Fix usb logging assignment
2026-05-26 Revert clock workaround
2026-05-26 Fix pinning bug
